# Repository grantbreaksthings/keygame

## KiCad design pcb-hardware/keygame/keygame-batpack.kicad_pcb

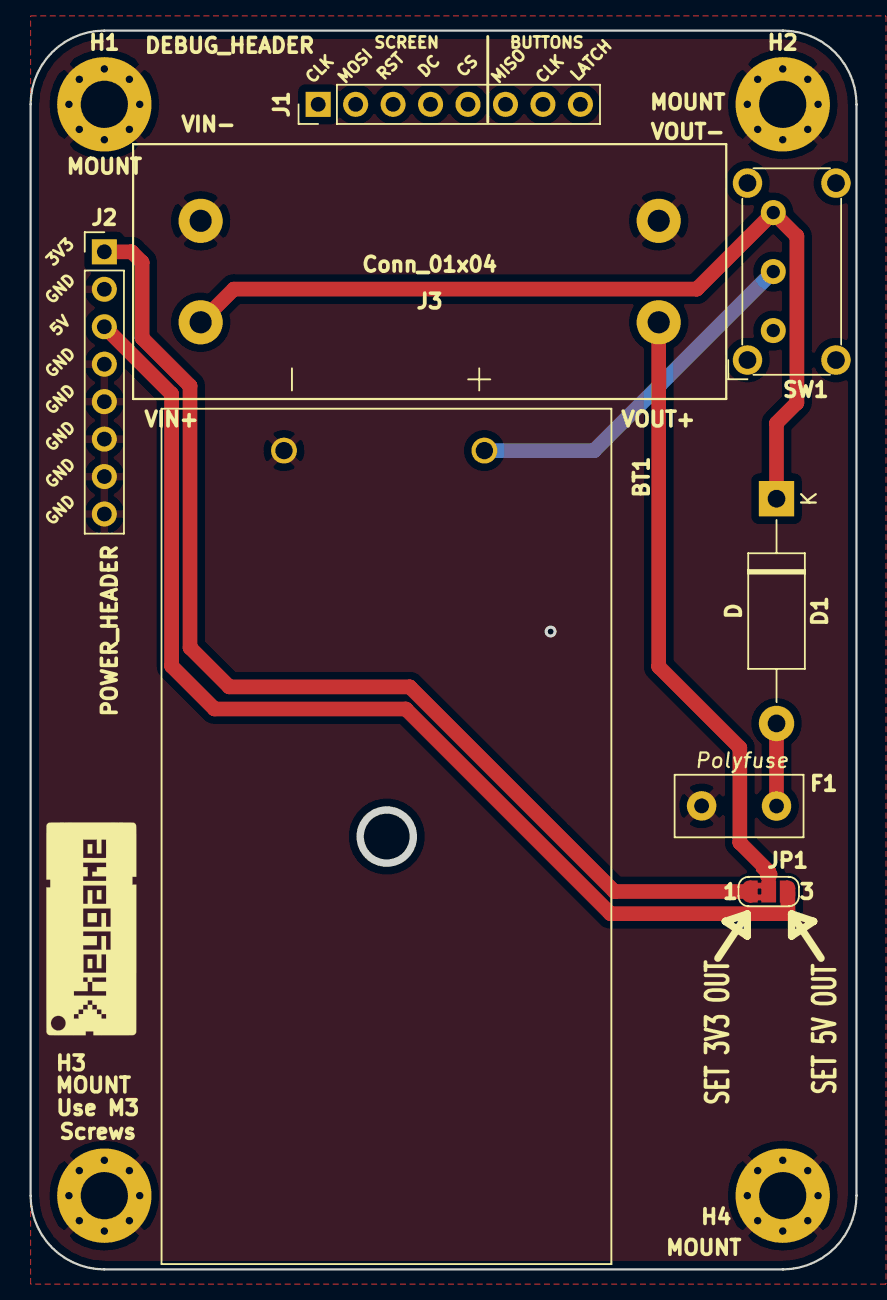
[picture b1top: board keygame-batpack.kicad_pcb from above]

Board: 2 copper layers, 55.6 x 83.6 mm, 12 parts (0 on the bottom side), 7 nets.

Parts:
BT1: Battery; BatteryHolder_BC2AAPC
D1: D; D_DO-15_P15.24mm_Horizontal
F1: Polyfuse; Fuse_Littelfuse_395Series
H1, H2, H3, H4: MOUNT; MountingHole_3.2mm_M3_Pad_Via
J1: DEBUG_HEADER; PinHeader_1x08_P2.54mm_Vertical
J2: POWER_HEADER; PinHeader_1x08_P2.54mm_Vertical
J3: Conn_01x04; MT3608_MODULE
JP1: Jumper_3_Bridged12; SolderJumper-3_P1.3mm_Bridged2Bar12_RoundedPad1.0x1.5mm_Num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
SW1: SW_SPDT; SW_E-Switch_EG1224_SPDT_Angled

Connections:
+3V3: J2.1, JP1.1
+5V: J2.3, JP1.3
GND: BT1.2, F1.2, H1.1, H2.1, H3.1, H4.1, J2.2, J2.4, J2.5, J2.6, J2.7, J2.8, J3.1, J3.4
unnamed: BT1.1, SW1.2
unnamed: D1.1, J3.3, SW1.3
unnamed: D1.2, F1.1
unnamed: J3.2, JP1.2

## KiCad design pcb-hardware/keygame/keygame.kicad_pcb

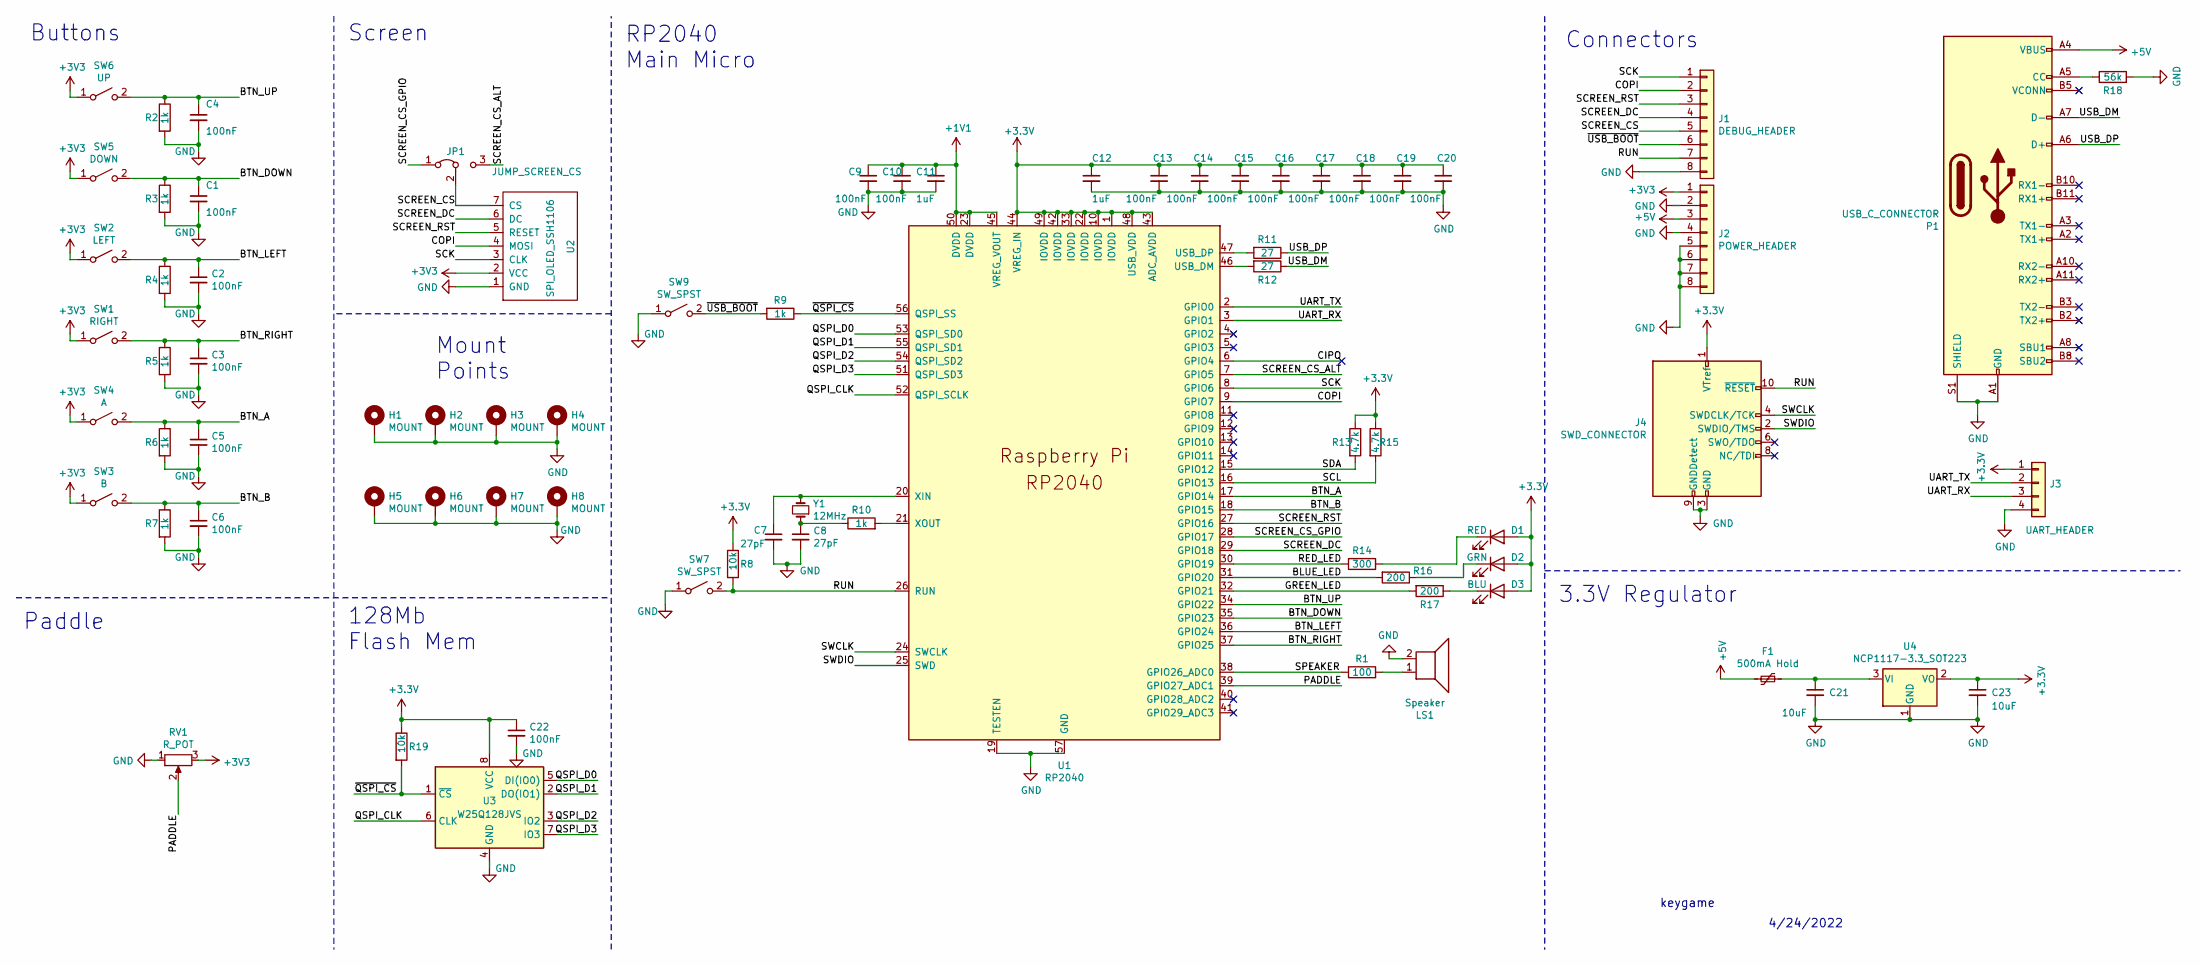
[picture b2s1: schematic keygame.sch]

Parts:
C1, C2, C3, C4, C5, C6, C9, C10, C13, C14, C15, C16, C17, C18, C19, C20, C22: 100nF; C_0402_1005Metric_Pad0.74x0.62mm_HandSolder
C7, C8: 27pF; C_0402_1005Metric_Pad0.74x0.62mm_HandSolder
C11, C12: 1uF; C_0805_2012Metric_Pad1.18x1.45mm_HandSolder
C21, C23: 10uF; C_1206_3216Metric_Pad1.33x1.80mm_HandSolder
D1: RED; LED_0402_1005Metric_Pad0.77x0.64mm_HandSolder
D2: GRN; LED_0402_1005Metric_Pad0.77x0.64mm_HandSolder
D3: BLU; LED_0402_1005Metric_Pad0.77x0.64mm_HandSolder
F1: 500mA Hold; Fuse_1206_3216Metric_Pad1.42x1.75mm_HandSolder
H1, H2, H3, H4, H5, H6, H7, H8: MOUNT; MountingHole_3.2mm_M3_Pad_Via
J1: DEBUG_HEADER; PinHeader_1x08_P2.54mm_Vertical
J2: POWER_HEADER; PinHeader_1x08_P2.54mm_Vertical
J3: UART_HEADER; PinHeader_1x04_P2.54mm_Vertical
J4: SWD_CONNECTOR; PinHeader_2x05_P1.27mm_Vertical_SMD
JP1: JUMP_SCREEN_CS; SolderJumper-3_P1.3mm_Bridged12_RoundedPad1.0x1.5mm
LS1: Speaker; PinHeader_1x02_P2.54mm_Vertical
P1: USB_C_CONNECTOR; USB_C_Receptacle_HRO_TYPE-C-31-M-12
R1: 100; R_0805_2012Metric_Pad1.20x1.40mm_HandSolder
R2, R3, R4, R5, R6, R7, R9, R10: 1k; R_0402_1005Metric_Pad0.72x0.64mm_HandSolder
R8, R19: 10k; R_0402_1005Metric_Pad0.72x0.64mm_HandSolder
R11, R12: 27; R_0603_1608Metric_Pad0.98x0.95mm_HandSolder
R13, R15: 4.7k; R_0402_1005Metric_Pad0.72x0.64mm_HandSolder
R14: 300; R_0402_1005Metric_Pad0.72x0.64mm_HandSolder
R16, R17: 200; R_0402_1005Metric_Pad0.72x0.64mm_HandSolder
R18: 56k; R_0402_1005Metric_Pad0.72x0.64mm_HandSolder
RV1: R_POT; Potentiometer_Bourns_PTV09A-1_Single_Vertical
SW1: RIGHT; SW_PUSH_6mm
SW2: LEFT; SW_PUSH_6mm
SW3: B; SW_PUSH_6mm
SW4: A; SW_PUSH_6mm
SW5: DOWN; SW_PUSH_6mm
SW6: UP; SW_PUSH_6mm
SW7, SW9: SW_SPST; SW_SPST_PTS810
U1: RP2040; RP2040-QFN-56
U2: SPI_OLED_SSH1106; SPI_OLED
U3: W25Q128JVS; SOIC-8_5.23x5.23mm_P1.27mm
U4: NCP1117-3.3_SOT223; SOT-223-3_TabPin2
Y1: 12MHz; Crystal_HC52-8mm_Vertical

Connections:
+1V1: C9.1, C10.1, C11.1, U1.23 (DVDD), U1.45 (VREG_VOUT), U1.50 (DVDD)
+5V: F1.2, J2.3, P1.A4 (VBUS), P1.A9 (VBUS), P1.B4 (VBUS), P1.B9 (VBUS)
/BLUE_LED: R16.2, U1.31 (GPIO20)
/BTN_A: C5.1, R6.1, SW4.2 (B), U1.17 (GPIO14)
/BTN_B: C6.1, R7.1, SW3.2 (B), U1.18 (GPIO15)
/BTN_DOWN: C1.1, R3.1, SW5.2 (B), U1.35 (GPIO23)
/BTN_LEFT: C2.1, R4.1, SW2.2 (B), U1.36 (GPIO24)
/BTN_RIGHT: C3.1, R5.1, SW1.2 (B), U1.37 (GPIO25)
/BTN_UP: C4.1, R2.1, SW6.2 (B), U1.34 (GPIO22)
/CIPO: U1.6 (GPIO4)
/COPI: J1.2, U1.9 (GPIO7), U2.4 (MOSI)
/GREEN_LED: R17.2, U1.32 (GPIO21)
/PADDLE: RV1.2, U1.39 (GPIO27_ADC1)
/QSPI_CLK: U1.52 (QSPI_SCLK), U3.6 (CLK)
/QSPI_D0: U1.53 (QSPI_SD0), U3.5 (DI(IO0))
/QSPI_D1: U1.55 (QSPI_SD1), U3.2 (DO(IO1))
/QSPI_D2: U1.54 (QSPI_SD2), U3.3 (IO2)
/QSPI_D3: U1.51 (QSPI_SD3), U3.7 (IO3)
/RED_LED: R14.2, U1.30 (GPIO19)
/RUN: J1.7, J4.10 (~RESET~), R8.2, SW7.2 (B), U1.26 (RUN)
/SCK: J1.1, U1.8 (GPIO6), U2.3 (CLK)
/SCL: R15.2, U1.16 (GPIO13)
/SCREEN_CS: J1.5, JP1.2 (C), U2.7 (CS)
/SCREEN_CS_ALT: JP1.3 (B), U1.7 (GPIO5)
/SCREEN_CS_GPIO: JP1.1 (A), U1.28 (GPIO17)
/SCREEN_DC: J1.4, U1.29 (GPIO18), U2.6 (DC)
/SCREEN_RST: J1.3, U1.27 (GPIO16), U2.5 (RESET)
/SDA: R13.2, U1.15 (GPIO12)
/SPEAKER: R1.1, U1.38 (GPIO26_ADC0)
/SWCLK: J4.4 (SWDCLK/TCK), U1.24 (SWCLK)
/SWDIO: J4.2 (SWDIO/TMS), U1.25 (SWD)
/UART_RX: J3.3, U1.3 (GPIO1)
/UART_TX: J3.2, U1.2 (GPIO0)
/USB_DM: P1.A7 (D-), R12.1
/USB_DP: P1.A6 (D+), R11.1
/~QSPI_CS: R9.1, R19.2, U1.56 (QSPI_SS), U3.1 (~CS)
/~USB_BOOT: J1.6, R9.2, SW9.2 (B)
GND: C1.2, C2.2, C3.2, C4.2, C5.2, C6.2, C7.2, C8.2, C9.2, C10.2, C11.2, C12.2, C13.2, C14.2, C15.2, C16.2, C17.2, C18.2, C19.2, C20.2, C21.2, C22.2, C23.2, H1.1, H2.1, H3.1, H4.1, H5.1, H6.1, H7.1, H8.1, J1.8, J2.2, J2.4, J2.5, J2.6, J2.7, J2.8, J3.4, J4.3 (GND), J4.5 (GND), J4.9 (GNDDetect), LS1.2, P1.A1 (GND), P1.A12 (GND), P1.B1 (GND), P1.B12 (GND), P1.S1 (SHIELD), R2.2, R3.2, R4.2, R5.2, R6.2, R7.2, R18.2, RV1.1, SW7.1 (A), SW9.1 (A), U1.19 (TESTEN), U1.57 (GND), U2.1 (GND), U3.4 (GND), U4.1 (GND)
unnamed: C7.1, U1.20 (XIN), Y1.2
unnamed: C8.1, R10.1, Y1.1
unnamed: C21.1, F1.1, U4.3 (VI)
unnamed: D1.1 (K), R14.1
unnamed: D2.1 (K), R16.1
unnamed: D3.1 (K), R17.1
unnamed: LS1.1, R1.2
unnamed: P1.A5 (CC), R18.1
unnamed: R10.2, U1.21 (XOUT)
unnamed: R11.2, U1.47 (USB_DP)
unnamed: R12.2, U1.46 (USB_DM)

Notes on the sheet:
Buttons
Paddle
Screen
Mount Points
keygame
4/24/2022
3.3V Regulator
RP2040 Main Micro
128Mb Flash Mem
Connectors

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
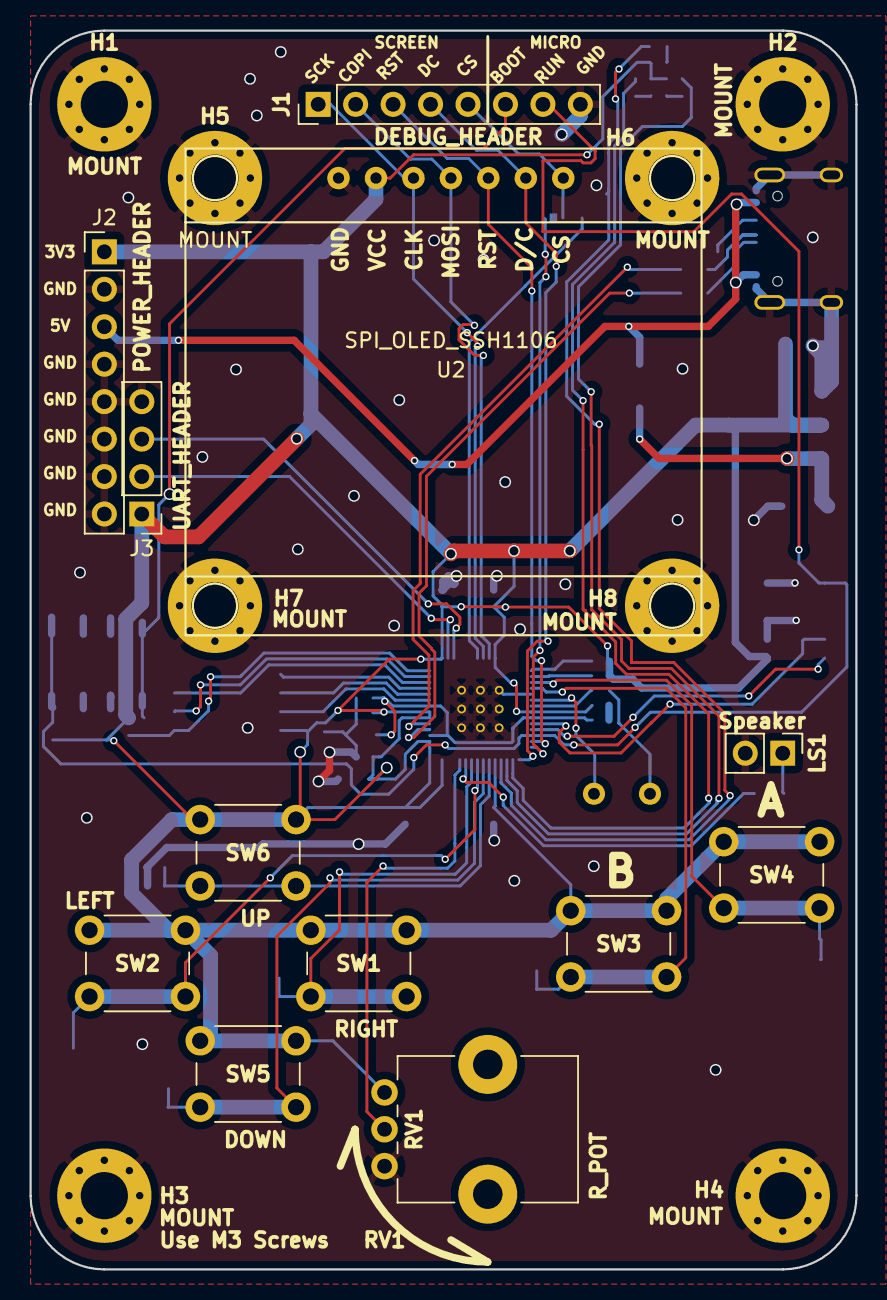
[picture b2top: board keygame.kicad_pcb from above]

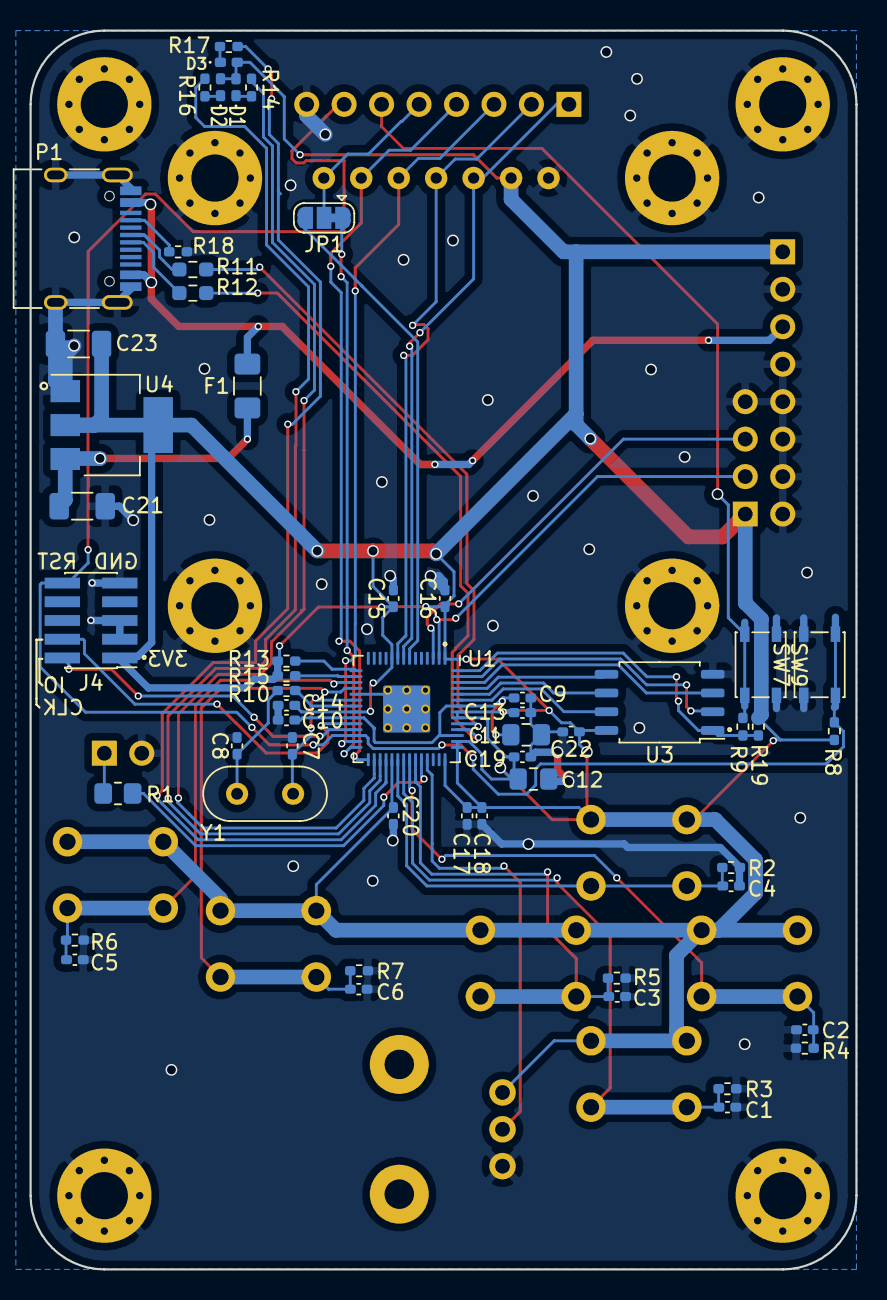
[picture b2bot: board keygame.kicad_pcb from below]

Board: 2 copper layers, 56.0 x 84.0 mm, 75 parts (55 on the bottom side), 49 nets.

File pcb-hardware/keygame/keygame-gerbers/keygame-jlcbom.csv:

Comment,Designator,Footprint,LCSC Part Number,Quantity
100nF,"C1,C2,C3,C4,C5,C6,C9,C10,C13,C14,C15,C16,C17,C18,C19,C20,C22",C_0402_1005Metric_Pad0.74x0.62mm_HandSolder,C1525,17
1uF,"C11,C12",C_0805_2012Metric_Pad1.18x1.45mm_HandSolder,C28323,2
10uF,"C21,C23",C_1206_3225Metric_Pad1.33x2.70mm_HandSolder,C13585,2
100,R1,R_0805_2012Metric_Pad1.20x1.40mm_HandSolder,C17408,1
1k,"R2,R3,R4,R5,R6,R7,R9,R10",R_0402_1005Metric_Pad0.72x0.64mm_HandSolder,C11702,8
10k,"R8,R19",R_0402_1005Metric_Pad0.72x0.64mm_HandSolder,C25744,2
4.7k,"R13,R15",R_0402_1005Metric_Pad0.72x0.64mm_HandSolder,C25900,2
56k,R18,R_0402_1005Metric_Pad0.72x0.64mm_HandSolder,C25796,1
RP2040,U1,RP2040-QFN-56,C2040,1
W25Q128JVS,U3,SOIC-8_5.23x5.23mm_P1.27mm,C97521,1
NCP1117-3.3_SOT223,U4,SOT-223-3_TabPin2,C6186,1
27pF,"C7,C8",C_0402_1005Metric_Pad0.74x0.62mm_HandSolder,C1557,2
USB_C_CONNECTOR,P1,USB_C_Receptacle_HRO_TYPE-C-31-M-12,C165948,1
27,"R11,R12",R_0603_1005Metric_Pad0.72x0.64mm_HandSolder,C25190,2
RED,D1,LED_0402_1005Metric_Pad0.77x0.64mm_HandSolder,C965790,1
GRN,D2,LED_0402_1005Metric_Pad0.77x0.64mm_HandSolder,C917188,1
BLU,D3,LED_0402_1005Metric_Pad0.77x0.64mm_HandSolder,C965795,1
300,R14,R_0402_1005Metric_Pad0.72x0.64mm_HandSolder,C25102,1
200,"R16,R17",R_0402_1005Metric_Pad0.72x0.64mm_HandSolder,C25087,2
SWD_CONNECTOR,J4,Arm SWD Connector,C150517,1
500mA Hold,F1,Fuse_1206,C163512,1

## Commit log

2022-06-06 moving to just the RP2040
2022-06-12 fixed J4
